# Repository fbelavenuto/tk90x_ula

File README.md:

# Projeto ULA CPLD - Clone da ULA do TK90X/TK95.

Este projeto se destina a substituir um componente feito sob medida para o microcomputador de 8 bits modelo TK90X e TK95, fabricado pela empresa brasileira Microdigital na década de 1980. O TK90X/TK95 é um clone do ZX Spectrum fabricado pela empresa inglesa Sinclair Research.

# Copyright

Copyright Fábio Belavenuto 2012.
Copyright Victor Trucco 2012.

# Licença

This documentation describes Open Hardware and is licensed under the CERN OHL v. 1.1.
You may redistribute and modify this documentation under the terms of the
CERN OHL v.1.1. (http://ohwr.org/cernohl). This documentation is distributed
WITHOUT ANY EXPRESS OR IMPLIED WARRANTY, INCLUDING OF MERCHANTABILITY,
SATISFACTORY QUALITY AND FITNESS FOR A PARTICULAR PURPOSE.
Please see the CERN OHL v.1.1 for applicable conditions

# Detalhes

Todo este trabalho foi baseado no trabalho do Chris Smith [1] e feito em conjunto pelos autores do projeto. Agradecimentos ao pessoal das listas de discussão brasileiras "ClubedoTK" [2] e "TK90X" [3] que incentivaram e ajudaram no desenvolvimento deste projeto.

No site [4] há um pequeno diário criado pelo Victor Trucco descrevendo os passos durante o desenvolvimento do projeto.

O projeto tem duas revisões, rev1 e rev2, cada uma delas em uma pasta separada. Em cada revisão existem uma pasta com o design da PCB, uma pasta com os aqruivos de fabricação Gerber e uma pasta com o projeto do código-fonte do CPLD. A versão do software utilizado para o design da PCB foi o Cadsoft Eagle e o software utilizado para o design do CPLD foi o Altera Quartus versão 10.1sp1.
  
Na pasta "VHDL Version" há uma versão do código do CPLD toda escrita em VHDL, tanto para CPLDs da Altera e CPLDs da Xilinx. Este código não foi usado no CPLD da ULA final.

Para a revisão 1, o arquivo [Pinout jumpers.jpg] "rev1/Pinout jumpers.jpg" mostra a pinagem dos jumpers e saída RGB contidas na PCB. Para a revisão 2 o mesmo pinout pode ser utilizado, porém a seleção do tipo de sincronismo é feita por jumpers de solda.

O produto final é uma placa pequena feita para ser inserida diretamente no soquete do circuito integrado original, substituindo assim o componente defeituoso, com a vantagem de ter uma saída RGB analógica em 15KHz para ser usado diretamente em monitores compatíveis.

A temporização deste projeto chega a 99% de fidelidade ao componente original.

# Montagem

Para a montagem da PCB, acesse [este](https://fbelavenuto.github.io/pages/ULA-rev1-ibom.html) link para BOM interativo da revisão 1 e [este](https://fbelavenuto.github.io/pages/ULA-rev2-ibom.html) para a revisão 2.

Solde os componentes SMD, consiga uma barra de terminais torneado de 80 pinos, corte-a no meio para os dois lados de 40 pinos. O CPLD ocupa o espaço de quatro pinos da barra de terminais torneada de cada lado, então é necessário cortar os 4 pinos centrais de cada barra para fazer uma soldagem em SMD nestes pontos.

Coloque a barra no lugar para descobrir quais os pinos devem ser cortados, corte com um alicate de corte fino para deixar rente à PCB. Utilize um soquete torneado de 40 pinos e plugue as barras no soquete, para uma soldagem alinhada. Coloque a PCB em cima da barra e encaixe os pinos não cortados nos seus respectivos furos e solde-os. Para soldar os 8 pinos cortados (4 de cada lado) coloque a ponta de ferro em um lado para aquecer a PCB e a barra de pinos ao mesmo tempo e coloque o estanho pelo outro lado. Confira com uma lente se a solda foi bem sucedida.

Se for utilizar a saída RGB 15KHz solde uma barra de pinos 90 graus na PCB, e na revisão 2 solde o jumper de solda do tipo de sincronismo. É possível escolher qual tipo de sincronismo irá para o monitor, separado ou composto. Dependendo do monitor um tipo poderá ser melhor que o outro, então pode ser necessário testar os dois tipos, porém a opção de sincronismo separado tem mais compatibilidade com os monitores.

Na pasta [Fotos](rev1/Fotos/) há algumas fotos do primeiro protótipo construido.

# Programação do CPLD

Para programar o CPLD é necessário um dispositivo USB Blaster específico para os CPLDs da Altera. Na PCB rev1 os pontos de contato dos sinais de programação estão espalhados pela PCB, sendo necessário a construção de uma "cama de pregos" ou a soldagem de fios nos pontos. Para a rev2 os sinais estão dispostos em um conector 1x6. O nome dos sinais estão no silkscreen da PCB. É necessário utilziar uma fonte externa de 5V e jogar 5V no pino VCC do USB Blaster, pois este não alimenta o dispositivo mas detecta se ele está alimentado.

Abra o projeto no software Quartus e vá até o programador. Alimente a PCB e o USB Blaster e clique em "Program". Caso haja falha neste passo cheque as conexões e cheque se está indo os 5V para o USB Blaster. O arquivo necessário para programar se chama "ULA.pof".

# Uso

É altamente recomendável a troca do soquete da ULA na PCB do TK90X/95 por um soquete torneado, porém é possível utilizar o original. Plugue com cuidado a PCB da ULA no soquete do TK, vá pressionando devagar para não entortar nenhum pino. Se tudo ocorrer bem é só ligar o micro e curtir a sua nova ULA.

Se for utilizar a saída RGB 15KHz construa um cabo com um conector DE-15 para ligar nos pinos de saída RGB conforme descrito [nesta](rev1/Pinout%20jumpers.jpg) imagem.

# Links

[1] http://www.zxdesign.info/thebeginning.shtml
[2] http://br.groups.yahoo.com/group/ClubedoTK/
[3] http://br.groups.yahoo.com/group/TK90X/
[4] http://www.victortrucco.com/TK/ULATKCPLD/ULATKCPLD.asp

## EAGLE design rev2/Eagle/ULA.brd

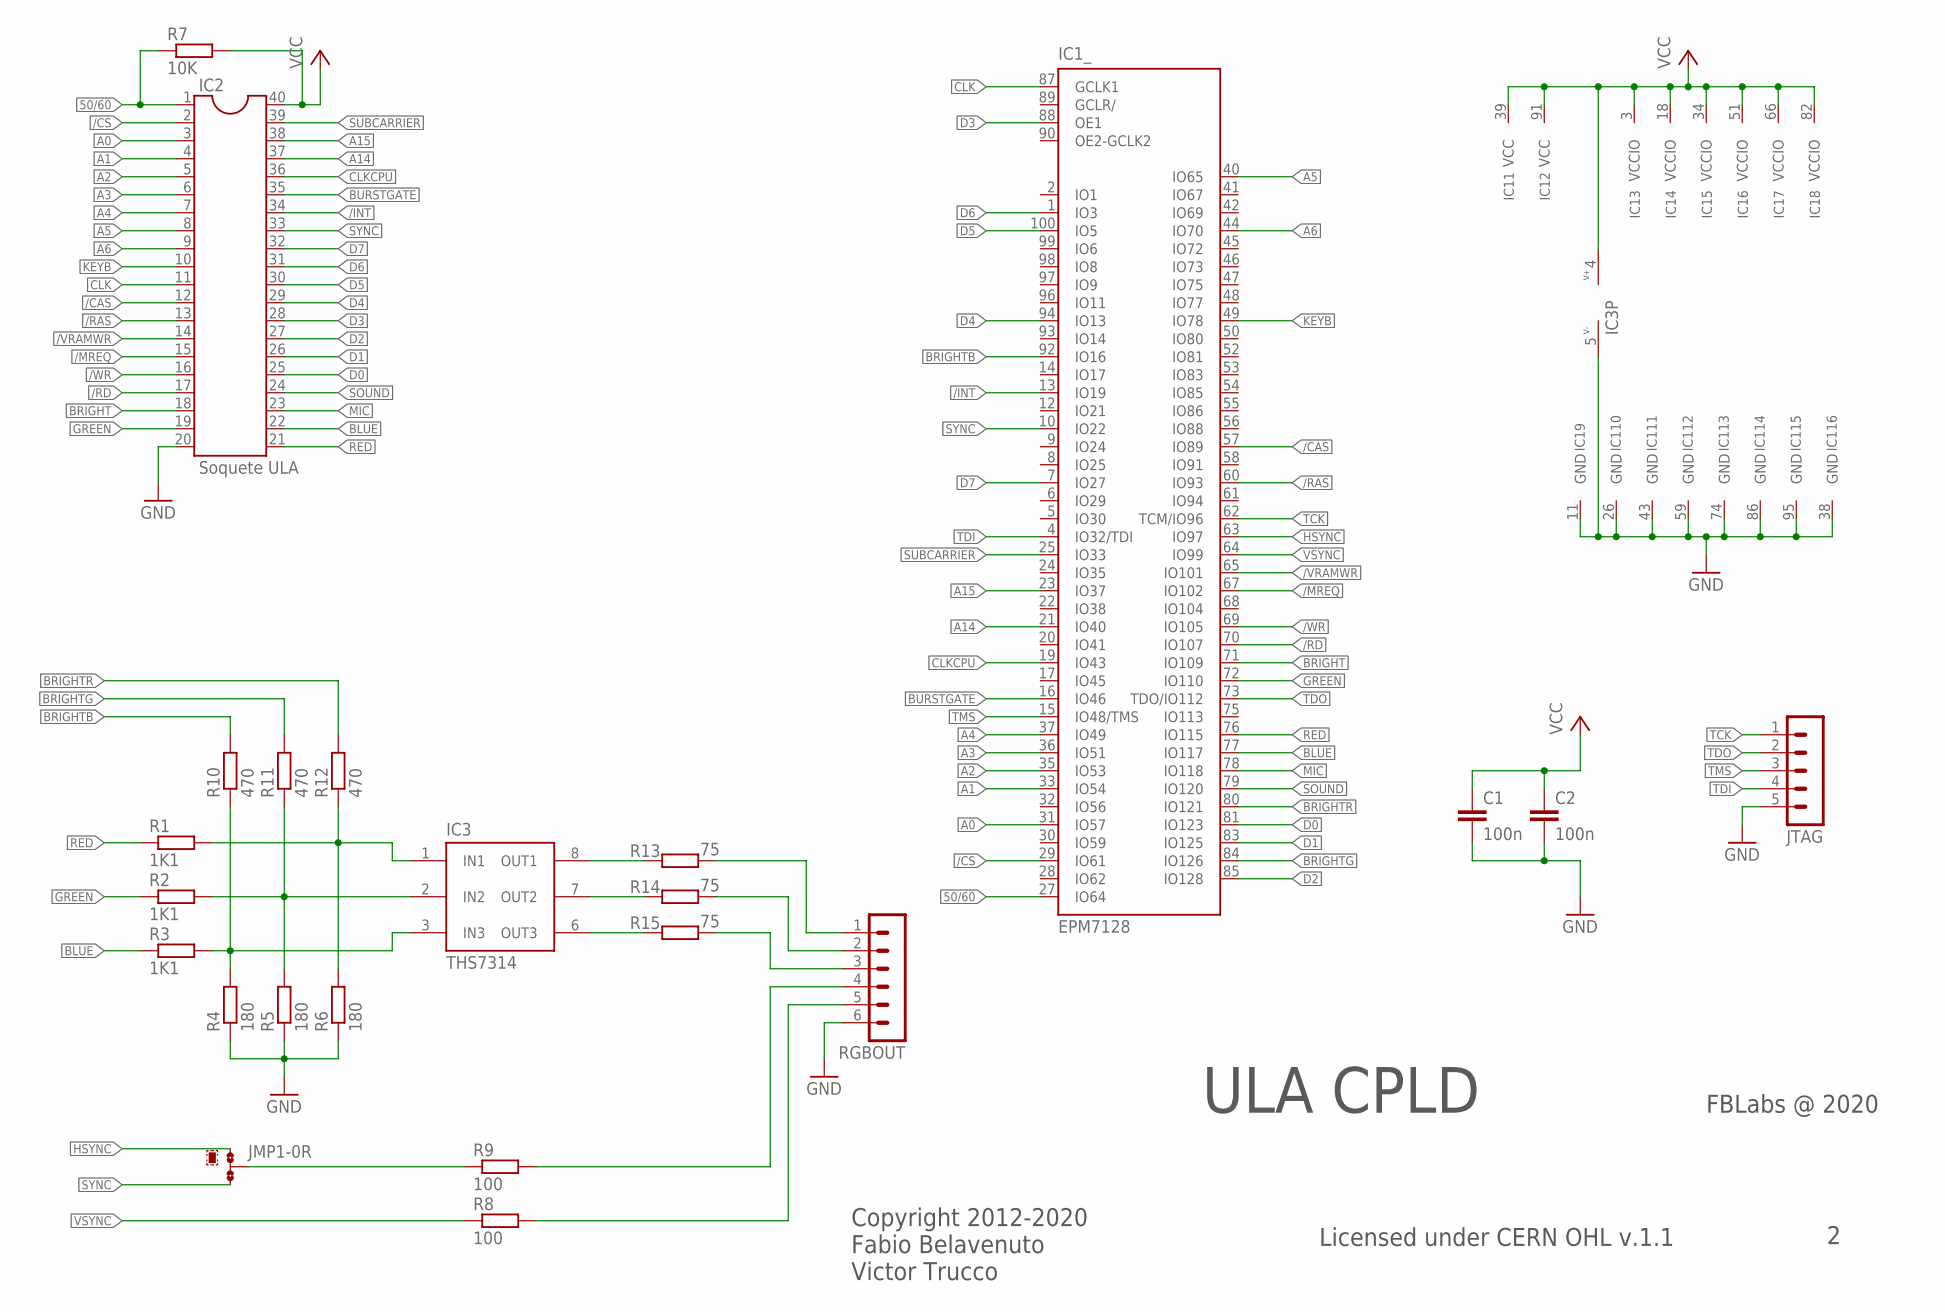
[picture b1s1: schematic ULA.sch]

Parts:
C1, C2: 100n; C1206
IC1: EPM7128; TQFP100
IC2: Soquete ULA; DIL40
IC3: THS7314; SOIC8
JMP1: 0R-JUMPA; A0R-JMP
JTAG: MA05-1
R1, R2, R3: 1K1; M0805
R4, R5, R6: 180; M0805
R7: 10K; M0805
R8, R9: 100; M0805
R10, R11, R12: 470; M0805
R13, R14, R15: 75; M0805
RGBOUT: MA06-1

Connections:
50/60: IC1.27 (IO64), IC2.1, R7.1
/CAS: IC1.57 (IO89), IC2.12
/CS: IC1.29 (IO61), IC2.2
/INT: IC1.13 (IO19), IC2.34
/MREQ: IC1.67 (IO102), IC2.15
/RAS: IC1.60 (IO93), IC2.13
/RD: IC1.70 (IO107), IC2.17
/VRAMWR: IC1.65 (IO101), IC2.14
/WR: IC1.69 (IO105), IC2.16
A0: IC1.31 (IO57), IC2.3
A1: IC1.33 (IO54), IC2.4
A2: IC1.35 (IO53), IC2.5
A3: IC1.36 (IO51), IC2.6
A4: IC1.37 (IO49), IC2.7
A5: IC1.40 (IO65), IC2.8
A6: IC1.44 (IO70), IC2.9
A14: IC1.21 (IO40), IC2.37
A15: IC1.23 (IO37), IC2.38
BLUE: IC1.77 (IO117), IC2.22, R3.1
BRIGHT: IC1.71 (IO109), IC2.18
BRIGHTB: IC1.92 (IO16), R10.2
BRIGHTG: IC1.84 (IO126), R11.2
BRIGHTR: IC1.80 (IO121), R12.2
BURSTGATE: IC1.16 (IO46), IC2.35
CLK: IC1.87 (GCLK1), IC2.11
CLKCPU: IC1.19 (IO43), IC2.36
D0: IC1.81 (IO123), IC2.25
D1: IC1.83 (IO125), IC2.26
D2: IC1.85 (IO128), IC2.27
D3: IC1.88 (OE1), IC2.28
D4: IC1.94 (IO13), IC2.29
D5: IC1.100 (IO5), IC2.30
D6: IC1.1 (IO3), IC2.31
D7: IC1.7 (IO27), IC2.32
GND: C1.2, C2.2, IC1.11 (GND), IC1.26 (GND), IC1.38 (GND), IC1.43 (GND), IC1.59 (GND), IC1.74 (GND), IC1.86 (GND), IC1.95 (GND), IC2.20, IC3.5 (V-), JTAG.5, R4.1, R5.1, R6.1, RGBOUT.6
GREEN: IC1.72 (IO110), IC2.19, R2.1
HSYNC: IC1.63 (IO97), JMP1.1
KEYB: IC1.49 (IO78), IC2.10
MIC: IC1.78 (IO118), IC2.23
unnamed: R15.2, RGBOUT.3
unnamed: R14.2, RGBOUT.2
unnamed: R13.2, RGBOUT.1
unnamed: IC3.3 (IN3), R3.2, R4.2, R10.1
unnamed: IC3.2 (IN2), R2.2, R5.2, R11.1
unnamed: IC3.6 (OUT3), R15.1
unnamed: IC3.7 (OUT2), R14.1
unnamed: IC3.8 (OUT1), R13.1
unnamed: IC3.1 (IN1), R1.2, R6.2, R12.1
unnamed: JMP1.2, R9.1
unnamed: R9.2, RGBOUT.4
unnamed: R8.2, RGBOUT.5
RED: IC1.76 (IO115), IC2.21, R1.1
SOUND: IC1.79 (IO120), IC2.24
SUBCARRIER: IC1.25 (IO33), IC2.39
SYNC: IC1.10 (IO22), IC2.33, JMP1.3
TCK: IC1.62 (TCM/IO96), JTAG.1
TDI: IC1.4 (IO32/TDI), JTAG.4
TDO: IC1.73 (TDO/IO112), JTAG.2
TMS: IC1.15 (IO48/TMS), JTAG.3
VCC: C1.1, C2.1, IC1.3 (VCCIO), IC1.18 (VCCIO), IC1.34 (VCCIO), IC1.39 (VCC), IC1.51 (VCCIO), IC1.66 (VCCIO), IC1.82 (VCCIO), IC1.91 (VCC), IC2.40, IC3.4 (V+), R7.2
VSYNC: IC1.64 (IO99), R8.1

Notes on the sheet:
ULA CPLD
Licensed under CERN OHL v.1.1
Copyright 2012-2020 Fabio Belavenuto Victor Trucco
FBLabs @ 2020

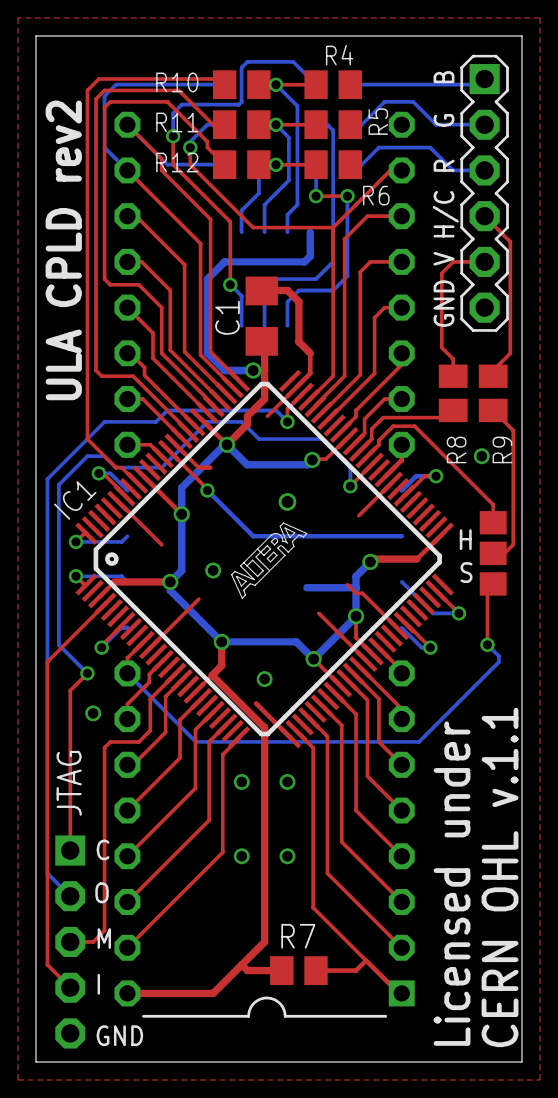
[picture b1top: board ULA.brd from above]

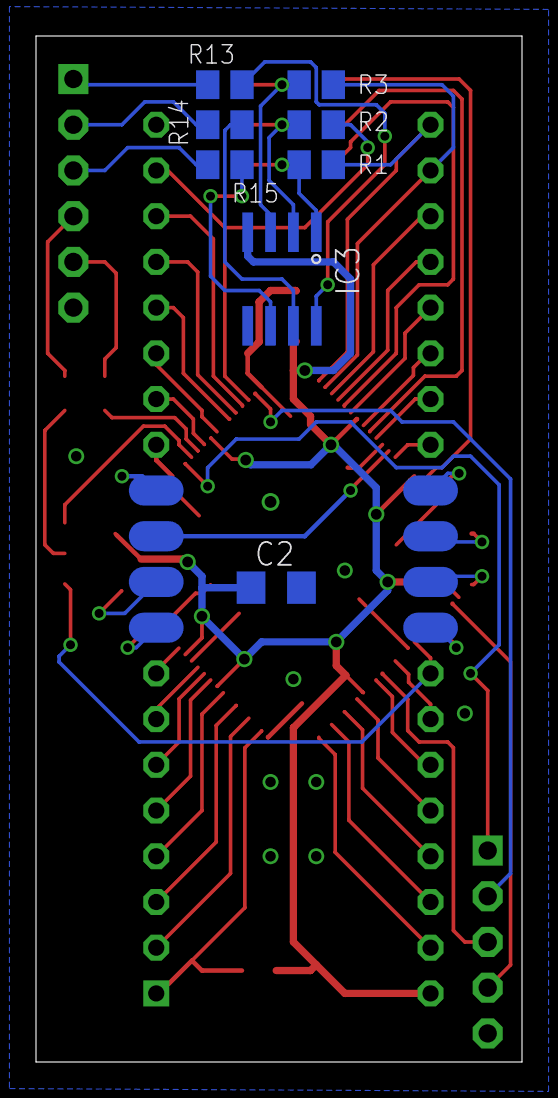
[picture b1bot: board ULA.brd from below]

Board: 2 copper layers, 27.0 x 57.0 mm, 23 parts (8 on the bottom side), 61 nets.

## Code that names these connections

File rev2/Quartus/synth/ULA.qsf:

# -------------------------------------------------------------------------- #
#
# Copyright (C) 1991-2011 Altera Corporation
# Your use of Altera Corporation's design tools, logic functions 
# and other software and tools, and its AMPP partner logic 
# functions, and any output files from any of the foregoing 
# (including device programming or simulation files), and any 
# associated documentation or information are expressly subject 
# to the terms and conditions of the Altera Program License 
# Subscription Agreement, Altera MegaCore Function License 
# Agreement, or other applicable license agreement, including, 
# without limitation, that your use is for the sole purpose of 
# programming logic devices manufactured by Altera and sold by 
# Altera or its authorized distributors.  Please refer to the 
# applicable agreement for further details.
#
# -------------------------------------------------------------------------- #
#
# Quartus II 64-Bit
# Version 10.1 Build 197 01/19/2011 Service Pack 1 SJ Web Edition
# Date created = 20:05:27  May 17, 2013
#
# -------------------------------------------------------------------------- #
#
# Notes:
#
# 1) The default values for assignments are stored in the file:
#		ULA_assignment_defaults.qdf
#    If this file doesn't exist, see file:
#		assignment_defaults.qdf
#
# 2) Altera recommends that you do not modify this file. This
#    file is updated automatically by the Quartus II software
#    and any changes you make may be lost or overwritten.
#
# -------------------------------------------------------------------------- #


set_global_assignment -name FAMILY MAX7000S
set_global_assignment -name DEVICE "EPM7128STC100-15"
set_global_assignment -name TOP_LEVEL_ENTITY ULA
set_global_assignment -name ORIGINAL_QUARTUS_VERSION "10.1 SP1"
set_global_assignment -name PROJECT_CREATION_TIME_DATE "20:05:27  MAY 17, 2013"
set_global_assignment -name LAST_QUARTUS_VERSION "13.0 SP1"
set_global_assignment -name DEVICE_FILTER_PACKAGE TQFP
set_global_assignment -name DEVICE_FILTER_PIN_COUNT 100
set_global_assignment -name ERROR_CHECK_FREQUENCY_DIVISOR 1702130533
set_global_assignment -name MIN_CORE_JUNCTION_TEMP 0
set_global_assignment -name MAX_CORE_JUNCTION_TEMP 85
set_global_assignment -name EDA_SIMULATION_TOOL "ModelSim-Altera (VHDL)"
set_global_assignment -name EDA_OUTPUT_DATA_FORMAT VHDL -section_id eda_simulation
set_global_assignment -name MAX7000_DEVICE_IO_STANDARD TTL
set_global_assignment -name PROJECT_OUTPUT_DIRECTORY output_files
set_global_assignment -name BDF_FILE ../src/Wait_Subcarrier.bdf
set_global_assignment -name BDF_FILE ../src/ULA.bdf
set_global_assignment -name BDF_FILE ../src/Porta254.bdf
set_global_assignment -name BDF_FILE ../src/HSync_Blank.bdf
set_global_assignment -name BDF_FILE ../src/DRAM_CAS_RAS.bdf
set_global_assignment -name BDF_FILE ../src/DRAM_ADDRESS.bdf
set_global_assignment -name BDF_FILE ../src/Display.bdf
set_global_assignment -name BDF_FILE ../src/clock.bdf
set_global_assignment -name VERILOG_FILE ../src/interrupcao2.v
set_global_assignment -name VERILOG_FILE ../src/counter_9bit.v
set_global_assignment -name VERILOG_FILE ../src/counter_13bit.v
set_global_assignment -name VERILOG_FILE ../src/counter_12bit.v
set_global_assignment -name VERILOG_FILE ../src/counter_10bit.v
set_global_assignment -name VHDL_FILE ../src/VSync2.vhd
set_global_assignment -name VHDL_FILE ../src/VoutGen.vhd
set_location_assignment PIN_7 -to d[7]
set_location_assignment PIN_1 -to d[6]
set_location_assignment PIN_100 -to d[5]
set_location_assignment PIN_94 -to d[4]
set_location_assignment PIN_88 -to d[3]
set_location_assignment PIN_85 -to d[2]
set_location_assignment PIN_83 -to d[1]
set_location_assignment PIN_81 -to d[0]
set_location_assignment PIN_27 -to PINO1_60/50Hz
set_location_assignment PIN_29 -to PINO2_/CS
set_location_assignment PIN_31 -to PINO3_A0
set_location_assignment PIN_33 -to PINO4_A1
set_location_assignment PIN_35 -to PINO5_A2
set_location_assignment PIN_36 -to PINO6_A3
set_location_assignment PIN_37 -to PINO7_A4
set_location_assignment PIN_40 -to PINO8_A5
set_location_assignment PIN_44 -to PINO9_A6
set_location_assignment PIN_49 -to PINO10_KEYBOARD
set_location_assignment PIN_87 -to PINO11_CLK
set_location_assignment PIN_57 -to PINO12_/CAS
set_location_assignment PIN_60 -to PINO13_/RAS
set_location_assignment PIN_65 -to PINO14_/VRAMWR
set_location_assignment PIN_67 -to PINO15_/MREQ
set_location_assignment PIN_69 -to PINO16_/WR
set_location_assignment PIN_70 -to PINO17_/RD
set_location_assignment PIN_71 -to PINO18_BRIGHT
set_location_assignment PIN_72 -to PINO19_GREEN
set_location_assignment PIN_76 -to PINO21_RED
set_location_assignment PIN_77 -to PINO22_BLUE
set_location_assignment PIN_78 -to PINO23_MIC
set_location_assignment PIN_79 -to PINO24_SOUND
set_location_assignment PIN_10 -to PINO33_SYNC
set_location_assignment PIN_13 -to PINO34_/INT
set_location_assignment PIN_16 -to PINO35_BURSTGATE
set_location_assignment PIN_19 -to PINO36_CLKCPU
set_location_assignment PIN_21 -to PINO37_A14
set_location_assignment PIN_23 -to PINO38_A15
set_location_assignment PIN_25 -to PINO39_SUBCARRIER
set_location_assignment PIN_63 -to _HSYNC
set_location_assignment PIN_64 -to _VSYNC
set_location_assignment PIN_92 -to BRIGHTB
set_location_assignment PIN_84 -to BRIGHTG
set_location_assignment PIN_80 -to BRIGHTR

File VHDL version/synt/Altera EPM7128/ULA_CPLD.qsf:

# -------------------------------------------------------------------------- #
#
# Copyright (C) 1991-2013 Altera Corporation
# Your use of Altera Corporation's design tools, logic functions 
# and other software and tools, and its AMPP partner logic 
# functions, and any output files from any of the foregoing 
# (including device programming or simulation files), and any 
# associated documentation or information are expressly subject 
# to the terms and conditions of the Altera Program License 
# Subscription Agreement, Altera MegaCore Function License 
# Agreement, or other applicable license agreement, including, 
# without limitation, that your use is for the sole purpose of 
# programming logic devices manufactured by Altera and sold by 
# Altera or its authorized distributors.  Please refer to the 
# applicable agreement for further details.
#
# -------------------------------------------------------------------------- #
#
# Quartus II 64-Bit
# Version 13.0.1 Build 232 06/12/2013 Service Pack 1 SJ Web Edition
# Date created = 17:55:27  November 14, 2013
#
# -------------------------------------------------------------------------- #
#
# Notes:
#
# 1) The default values for assignments are stored in the file:
#		ULA_CPLD_assignment_defaults.qdf
#    If this file doesn't exist, see file:
#		assignment_defaults.qdf
#
# 2) Altera recommends that you do not modify this file. This
#    file is updated automatically by the Quartus II software
#    and any changes you make may be lost or overwritten.
#
# -------------------------------------------------------------------------- #


set_global_assignment -name FAMILY MAX7000S
set_global_assignment -name DEVICE "EPM7128STC100-10"
set_global_assignment -name TOP_LEVEL_ENTITY ula
set_global_assignment -name ORIGINAL_QUARTUS_VERSION "13.0 SP1"
set_global_assignment -name PROJECT_CREATION_TIME_DATE "17:55:26  NOVEMBER 14, 2013"
set_global_assignment -name LAST_QUARTUS_VERSION "13.0 SP1"
set_global_assignment -name PROJECT_OUTPUT_DIRECTORY output_files
set_global_assignment -name DEVICE_FILTER_PACKAGE TQFP
set_global_assignment -name DEVICE_FILTER_PIN_COUNT 100
set_global_assignment -name ERROR_CHECK_FREQUENCY_DIVISOR "-1"
set_global_assignment -name OPTIMIZE_HOLD_TIMING OFF
set_global_assignment -name OPTIMIZE_MULTI_CORNER_TIMING OFF
set_global_assignment -name FITTER_EFFORT "STANDARD FIT"
set_global_assignment -name VHDL_FILE ../../src/ula.vhd
set_global_assignment -name VHDL_FILE ../../src/top.vhd
set_global_assignment -name EDA_SIMULATION_TOOL "ModelSim-Altera (VHDL)"
set_global_assignment -name EDA_OUTPUT_DATA_FORMAT VHDL -section_id eda_simulation
set_global_assignment -name MAX7000_DEVICE_IO_STANDARD TTL
set_location_assignment PIN_7 -to ULA_D[7]
set_location_assignment PIN_1 -to ULA_D[6]
set_location_assignment PIN_100 -to ULA_D[5]
set_location_assignment PIN_94 -to ULA_D[4]
set_location_assignment PIN_88 -to ULA_D[3]
set_location_assignment PIN_85 -to ULA_D[2]
set_location_assignment PIN_83 -to ULA_D[1]
set_location_assignment PIN_81 -to ULA_D[0]
set_location_assignment PIN_27 -to VERT50_60
set_location_assignment PIN_69 -to WR
set_location_assignment PIN_77 -to BLUE
set_location_assignment PIN_71 -to BRIGHT
set_location_assignment PIN_16 -to BURSTGATE
set_location_assignment PIN_19 -to CPU
set_location_assignment PIN_10 -to CSYNC
set_location_assignment PIN_72 -to GREEN
set_location_assignment PIN_63 -to HSYNC
set_location_assignment PIN_13 -to INT
set_location_assignment PIN_49 -to KEYBOARD
set_location_assignment PIN_78 -to MIC
set_location_assignment PIN_76 -to RED
set_location_assignment PIN_79 -to SOUND
set_location_assignment PIN_25 -to SUBCARRIER
set_location_assignment PIN_44 -to VRAM_A[6]
set_location_assignment PIN_40 -to VRAM_A[5]
set_location_assignment PIN_37 -to VRAM_A[4]
set_location_assignment PIN_36 -to VRAM_A[3]
set_location_assignment PIN_35 -to VRAM_A[2]
set_location_assignment PIN_33 -to VRAM_A[1]
set_location_assignment PIN_31 -to VRAM_A[0]
set_location_assignment PIN_57 -to VRAM_CAS
set_location_assignment PIN_60 -to VRAM_RAS
set_location_assignment PIN_65 -to VRAM_WR
set_location_assignment PIN_64 -to VSYNC
set_location_assignment PIN_21 -to A14
set_location_assignment PIN_23 -to A15
set_location_assignment PIN_29 -to CS
set_location_assignment PIN_67 -to MREQ
set_location_assignment PIN_87 -to OSC
set_location_assignment PIN_70 -to RD
set_global_assignment -name MAX7000_OPTIMIZATION_TECHNIQUE SPEED
set_global_assignment -name SYNTH_TIMING_DRIVEN_SYNTHESIS OFF

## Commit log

2019-09-08 First upload
2024-06-01 Organização e documentação
